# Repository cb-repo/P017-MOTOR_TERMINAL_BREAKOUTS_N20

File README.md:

# N20 MOTOR TERMINAL BREAKOUTS v1.0 (2-pack)

Motor terminals are traditionally small and flimsy, making it hard to guarantee a reliable solder connection.
MOTOR TERMINAL BREAKOUTS are designed to simplify and strengthen these solder joints, enabling more reliable operation especally in high vibration environments: orignially designed for combat robotics but is suitable for any application using these motors. 
  
Developed, assembled, and tested in [Christchurch, New Zealand](https://www.google.co.nz/maps/place/Christchurch+New+Zealand), by Connor Benton.

## FEATURES
- Fits all N-series (N10 / N20 / N30) motors.
- Mounts to the motor at 0°, 45°, 90°, and 135° angles.
- Large pads with holes to enable stronger connections to the wires.
- Pads are broken out onto PCB fingers allowing the wires to be heatshrunk post soldering (providing even greater mechanical strength).
- 100nF capacitor across the motor output to filter noise and voltage spikes.

## SPECIFICATIONS
- **Dimensions:** 10x15x1 mm
- **Weight:** 1g each
- **Material:** Fiberglass (FR4)
- **Mounting Pad Center:** 7.5mm
- **Included in Package:** 2x N20 Motor Terminal Breakouts

## PACKAGE INCLUDES

- 2x N20 MOTOR TERMINAL BREAKOUTS

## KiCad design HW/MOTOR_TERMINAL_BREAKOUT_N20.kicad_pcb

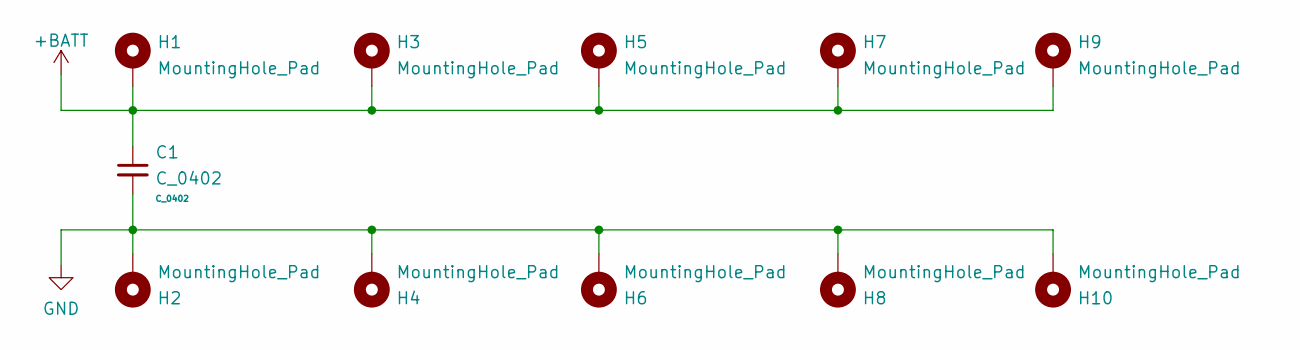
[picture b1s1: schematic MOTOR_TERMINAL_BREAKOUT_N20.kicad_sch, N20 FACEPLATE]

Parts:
C1: C_0402
H1, H2: MountingHole_Pad; MountingHole_2.2mm_M2_Pad_TopBottom
H3, H4, H5, H6, H7, H8, H9, H10: MountingHole_Pad; MountingHole_3mm_Pad_TopBottom

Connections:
+BATT: C1.1, H1.1, H3.1, H5.1, H7.1, H9.1
GND: C1.2, H2.1, H4.1, H6.1, H8.1, H10.1

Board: 2 copper layers, 12 parts (0 on the bottom side), 2 nets, no tracks yet.

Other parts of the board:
H13: MountingHole_Pad; MountingHole_6.5mm

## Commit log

2022-07-19 Initialise LFS in Repo
2022-07-31 Generate First Revision N20 Breakout
2022-08-09 Update README for release to CRNZ
2025-06-12 Create v1.0 Readme
2025-09-16 Update Datasheet for v1.1 Hardware
